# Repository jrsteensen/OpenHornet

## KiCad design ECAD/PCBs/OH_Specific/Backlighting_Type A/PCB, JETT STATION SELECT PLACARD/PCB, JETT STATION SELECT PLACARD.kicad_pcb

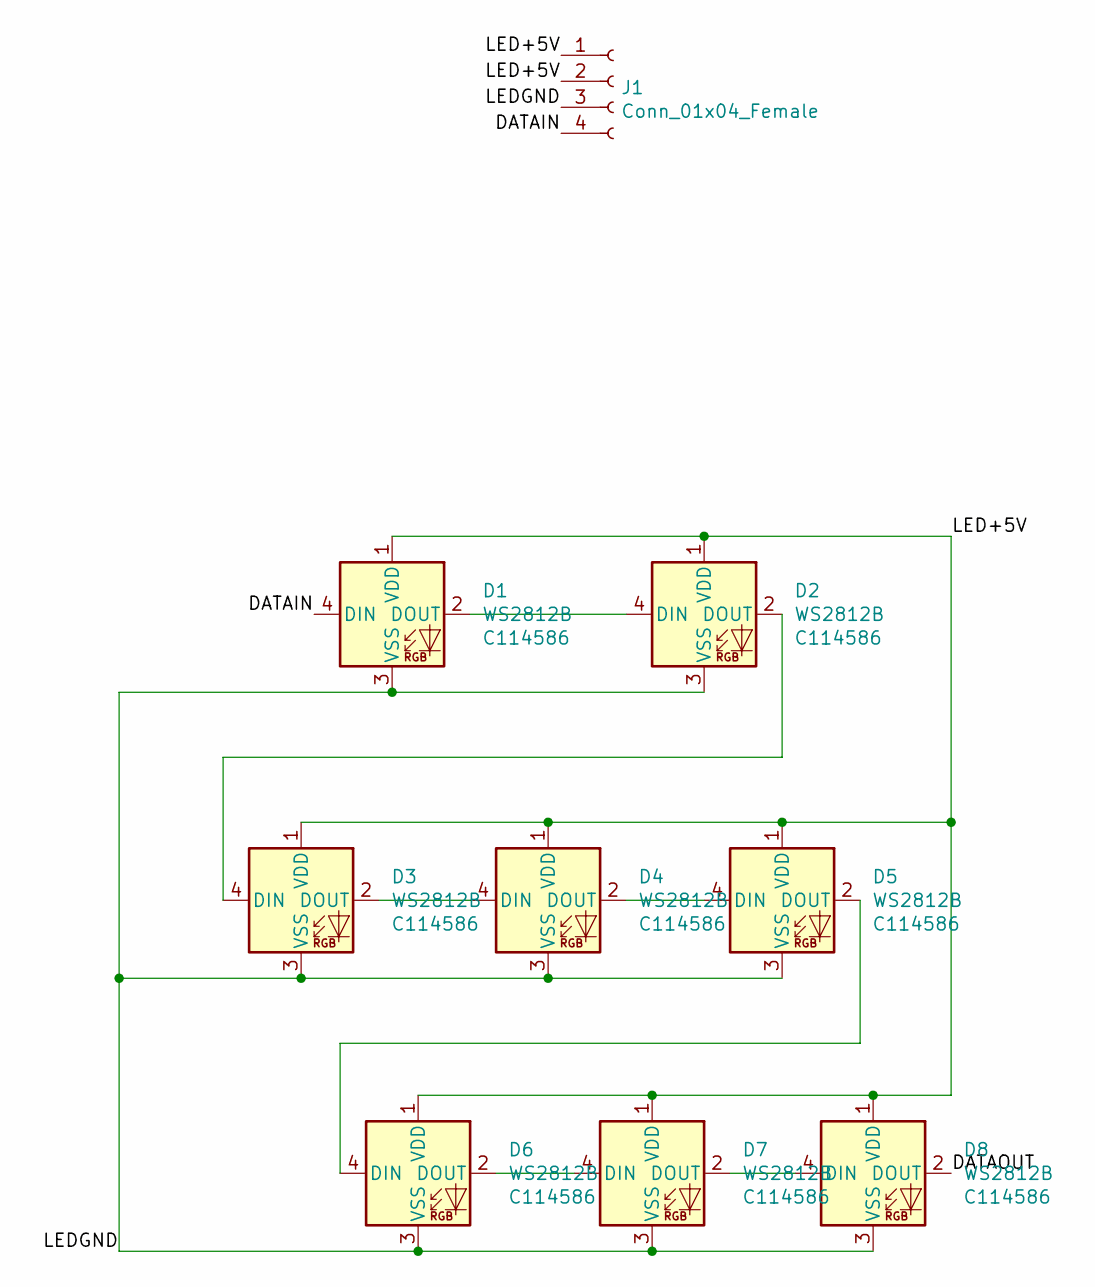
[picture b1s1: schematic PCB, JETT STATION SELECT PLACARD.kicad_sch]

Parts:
D1, D2, D3, D4, D5, D6, D7, D8: WS2812B; LED_WS2812B_PLCC4_5.0x5.0mm_P3.2mm; LCSC Part Number C114586
J1: Conn_01x04_Female; Molex_Mini-Fit_Jr_5566-04A_2x02_P4.20mm_Vertical

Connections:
/DATAIN: D1.4 (DIN), J1.4
/DATAOUT: D8.2 (DOUT)
/LED+5V: D1.1 (VDD), D2.1 (VDD), D3.1 (VDD), D4.1 (VDD), D5.1 (VDD), D6.1 (VDD), D7.1 (VDD), D8.1 (VDD), J1.1, J1.2
/LEDGND: D1.3 (VSS), D2.3 (VSS), D3.3 (VSS), D4.3 (VSS), D5.3 (VSS), D6.3 (VSS), D7.3 (VSS), D8.3 (VSS), J1.3
unnamed: D1.2 (DOUT), D2.4 (DIN)
unnamed: D2.2 (DOUT), D3.4 (DIN)
unnamed: D3.2 (DOUT), D4.4 (DIN)
unnamed: D4.2 (DOUT), D5.4 (DIN)
unnamed: D5.2 (DOUT), D6.4 (DIN)
unnamed: D6.2 (DOUT), D7.4 (DIN)
unnamed: D7.2 (DOUT), D8.4 (DIN)

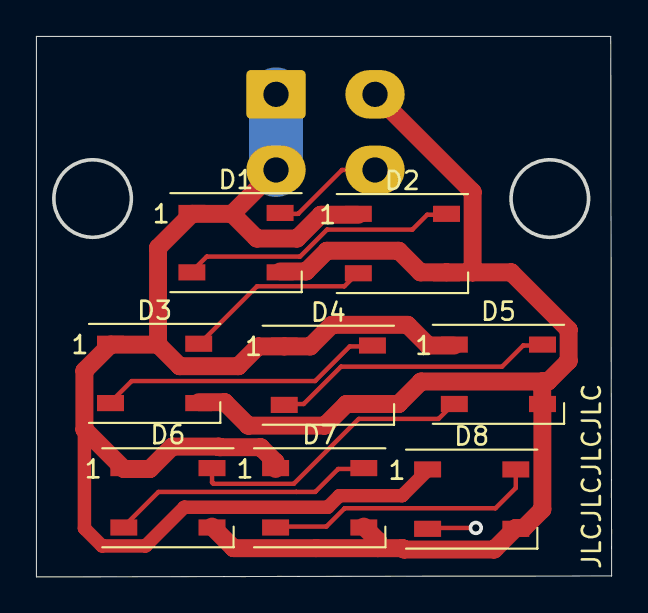
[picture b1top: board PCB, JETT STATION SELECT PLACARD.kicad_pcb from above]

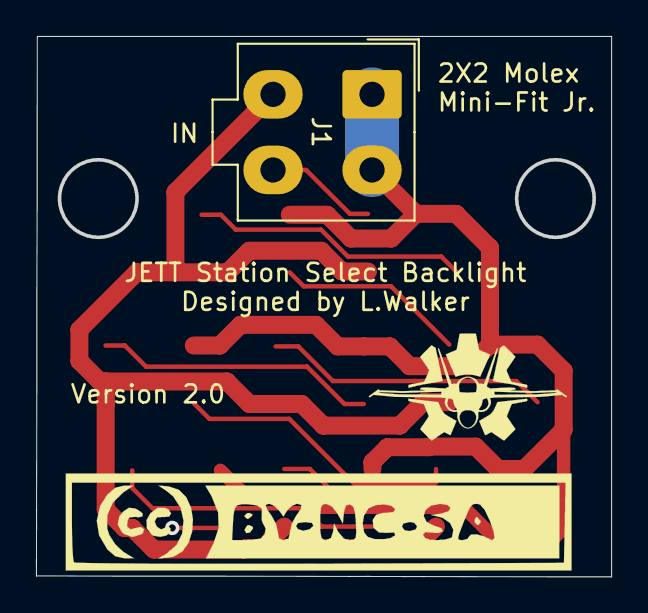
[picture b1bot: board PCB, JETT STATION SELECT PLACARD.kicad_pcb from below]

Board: 2 copper layers, 32.0 x 30.0 mm, 11 parts (3 on the bottom side), 10 nets.

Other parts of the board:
G1: OH_LOGO_ONLY_11x6mm
G2: LOGO; CC-BY-NC-SA-Small

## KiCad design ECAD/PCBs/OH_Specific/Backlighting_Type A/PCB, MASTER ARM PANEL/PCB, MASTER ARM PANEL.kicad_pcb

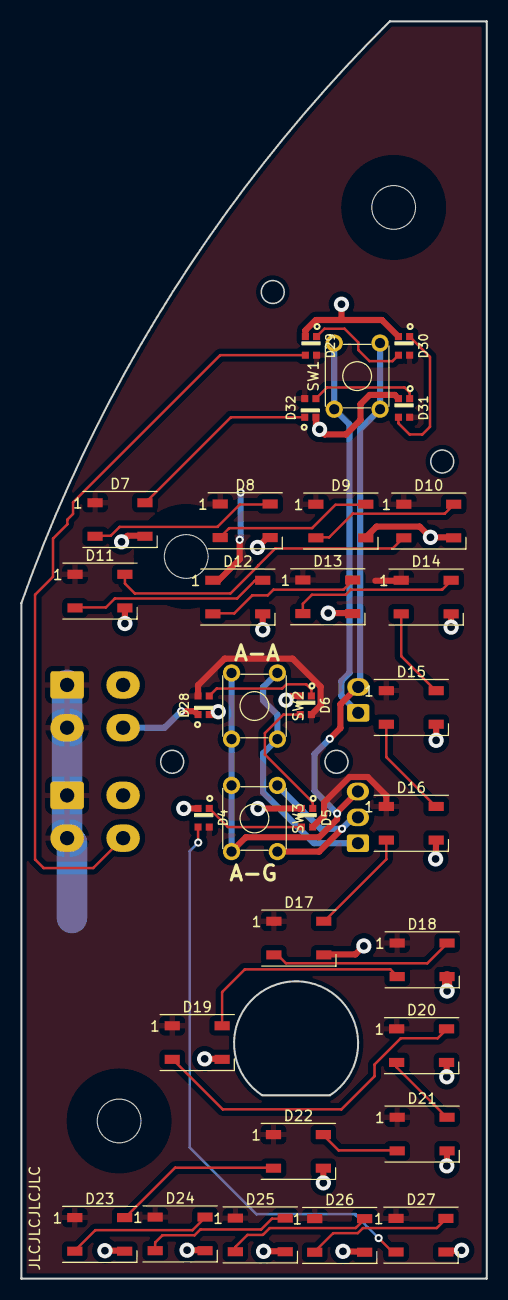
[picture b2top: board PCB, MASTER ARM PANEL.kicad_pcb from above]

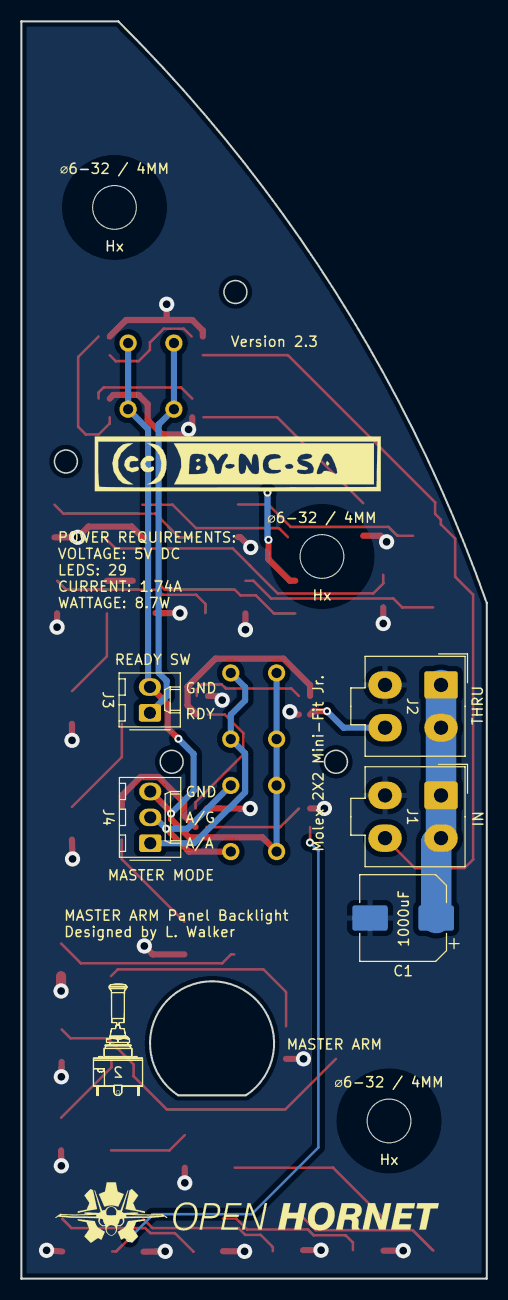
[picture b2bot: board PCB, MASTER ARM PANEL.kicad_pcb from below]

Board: 2 copper layers, 45.7 x 123.5 mm, 43 parts (7 on the bottom side), 36 nets.

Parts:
C1: C_Polarized; CP_Elec_8x10
D4, D5, D6, D28, D29, D30, D31, D32: WS2812B-2020; WS2812-2020
D7, D8, D9, D10, D11, D12, D13, D14, D15, D16, D17, D18, D19, D20, D21, D22, D23, D24, D25, D26, D27: WS2812B; LED_WS2812B_PLCC4_5.0x5.0mm_P3.2mm
H1, H2, H3: OHPanelScrew; OH_Panel_6-32_PHS
J1: BL IN; Molex_Mini-Fit_Jr_5566-04A_2x02_P4.20mm_Vertical
J2: BL OUT; Molex_Mini-Fit_Jr_5566-04A_2x02_P4.20mm_Vertical
J3: READY; Molex_KK-254_AE-6410-02A_1x02_P2.54mm_Vertical
J4: MASTER MODE; Molex_KK-254_AE-6410-03A_1x03_P2.54mm_Vertical
LOGO1: CC-BY-NC-SA_Icon; CC-BY-NC-SA-Small
LOGO2: OpenHornetLogoSmall; OH_LOGO_37.7mm_5.9mm
LOGO3: OH_S2AL_Silkscreen; S2AL_Toggle_Silkscreen
SW1: READY; SW_TH_Tactile_Omron_B3F-10xx
SW2: A/A; SW_TH_Tactile_Omron_B3F-10xx
SW3: A/G; SW_TH_Tactile_Omron_B3F-10xx

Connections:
/AA_SW: J4.1, SW2.1, SW2.2
/AG_SW: J4.2, SW3.1, SW3.2
/DATAIN: D29.3 (DIN), J1.4
/DATAOUT: D28.1 (DOUT), J2.4
/LED+5V: C1.1, D4.4 (VSS), D5.4 (VSS), D6.4 (VSS), D7.1 (VDD), D8.1 (VDD), D9.1 (VDD), D10.1 (VDD), D11.1 (VDD), D12.1 (VDD), D13.1 (VDD), D14.1 (VDD), D15.1 (VDD), D16.1 (VDD), D17.1 (VDD), D18.1 (VDD), D19.1 (VDD), D20.1 (VDD), D21.1 (VDD), D22.1 (VDD), D23.1 (VDD), D24.1 (VDD), D25.1 (VDD), D26.1 (VDD), D27.1 (VDD), D28.4 (VSS), D29.4 (VSS), D30.4 (VSS), D31.4 (VSS), D32.4 (VSS), J1.1, J1.2, J2.1, J2.2
/LEDGND: C1.2, D4.2 (GND), D5.2 (GND), D6.2 (GND), D7.3 (VSS), D8.3 (VSS), D9.3 (VSS), D10.3 (VSS), D11.3 (VSS), D12.3 (VSS), D13.3 (VSS), D14.3 (VSS), D15.3 (VSS), D16.3 (VSS), D17.3 (VSS), D18.3 (VSS), D19.3 (VSS), D20.3 (VSS), D21.3 (VSS), D22.3 (VSS), D23.3 (VSS), D24.3 (VSS), D25.3 (VSS), D26.3 (VSS), D27.3 (VSS), D28.2 (GND), D29.2 (GND), D30.2 (GND), D31.2 (GND), D32.2 (GND), J1.3, J2.3
/READY_SW: J3.1, SW1.1, SW1.2
GND: J3.2, J4.3, SW1.3, SW1.4, SW2.3, SW2.4, SW3.3, SW3.4
unnamed: D4.1 (DOUT), D5.3 (DIN)
unnamed: D5.1 (DOUT), D6.3 (DIN)
unnamed: D7.2 (DOUT), D8.4 (DIN)
unnamed: D8.2 (DOUT), D9.4 (DIN)
unnamed: D10.2 (DOUT), D11.4 (DIN)
unnamed: D9.2 (DOUT), D10.4 (DIN)
unnamed: D11.2 (DOUT), D12.4 (DIN)
unnamed: D12.2 (DOUT), D13.4 (DIN)
unnamed: D13.2 (DOUT), D14.4 (DIN)
unnamed: D14.2 (DOUT), D15.4 (DIN)
unnamed: D15.2 (DOUT), D16.4 (DIN)
unnamed: D16.2 (DOUT), D17.4 (DIN)
unnamed: D17.2 (DOUT), D18.4 (DIN)
unnamed: D18.2 (DOUT), D19.4 (DIN)
unnamed: D19.2 (DOUT), D20.4 (DIN)
unnamed: D20.2 (DOUT), D21.4 (DIN)
unnamed: D21.2 (DOUT), D22.4 (DIN)
unnamed: D22.2 (DOUT), D23.4 (DIN)
unnamed: D23.2 (DOUT), D24.4 (DIN)
unnamed: D24.2 (DOUT), D25.4 (DIN)
unnamed: D25.2 (DOUT), D26.4 (DIN)
unnamed: D26.2 (DOUT), D27.4 (DIN)
unnamed: D4.3 (DIN), D27.2 (DOUT)
unnamed: D6.1 (DOUT), D28.3 (DIN)
unnamed: D29.1 (DOUT), D30.3 (DIN)
unnamed: D30.1 (DOUT), D31.3 (DIN)
unnamed: D31.1 (DOUT), D32.3 (DIN)
unnamed: D7.4 (DIN), D32.1 (DOUT)

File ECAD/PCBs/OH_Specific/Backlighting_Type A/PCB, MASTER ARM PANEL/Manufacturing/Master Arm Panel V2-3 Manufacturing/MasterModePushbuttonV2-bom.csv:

Comment,Designator,Footprint,LCSC
C_Polarized,C1,Capacitor_SMD:CP_Elec_8x10,
WS2812B-2020,"D4,D5,D6,D28,D29,D30,D31,D32",KiCAD Libraries:WS2812-2020,C965555
WS2812B,"D7,D8,D9,D10,D11,D12,D13,D14,D15,D16,D17,D18,D19,D20,D21,D22,D23,D24,D25,D26,D27",LED_SMD:LED_WS2812B_PLCC4_5.0x5.0mm_P3.2mm,C2761795
BL IN,J1,Connector_Molex:Molex_Mini-Fit_Jr_5566-04A_2x02_P4.20mm_Vertical,
BL OUT,J2,Connector_Molex:Molex_Mini-Fit_Jr_5566-04A_2x02_P4.20mm_Vertical,
READY,J3,Connector_Molex:Molex_KK-254_AE-6410-02A_1x02_P2.54mm_Vertical,
MASTER MODE,J4,Connector_Molex:Molex_KK-254_AE-6410-03A_1x03_P2.54mm_Vertical,
READY,SW1,Button_Switch_THT:SW_TH_Tactile_Omron_B3F-10xx,
A/A,SW2,Button_Switch_THT:SW_TH_Tactile_Omron_B3F-10xx,
A/G,SW3,Button_Switch_THT:SW_TH_Tactile_Omron_B3F-10xx,

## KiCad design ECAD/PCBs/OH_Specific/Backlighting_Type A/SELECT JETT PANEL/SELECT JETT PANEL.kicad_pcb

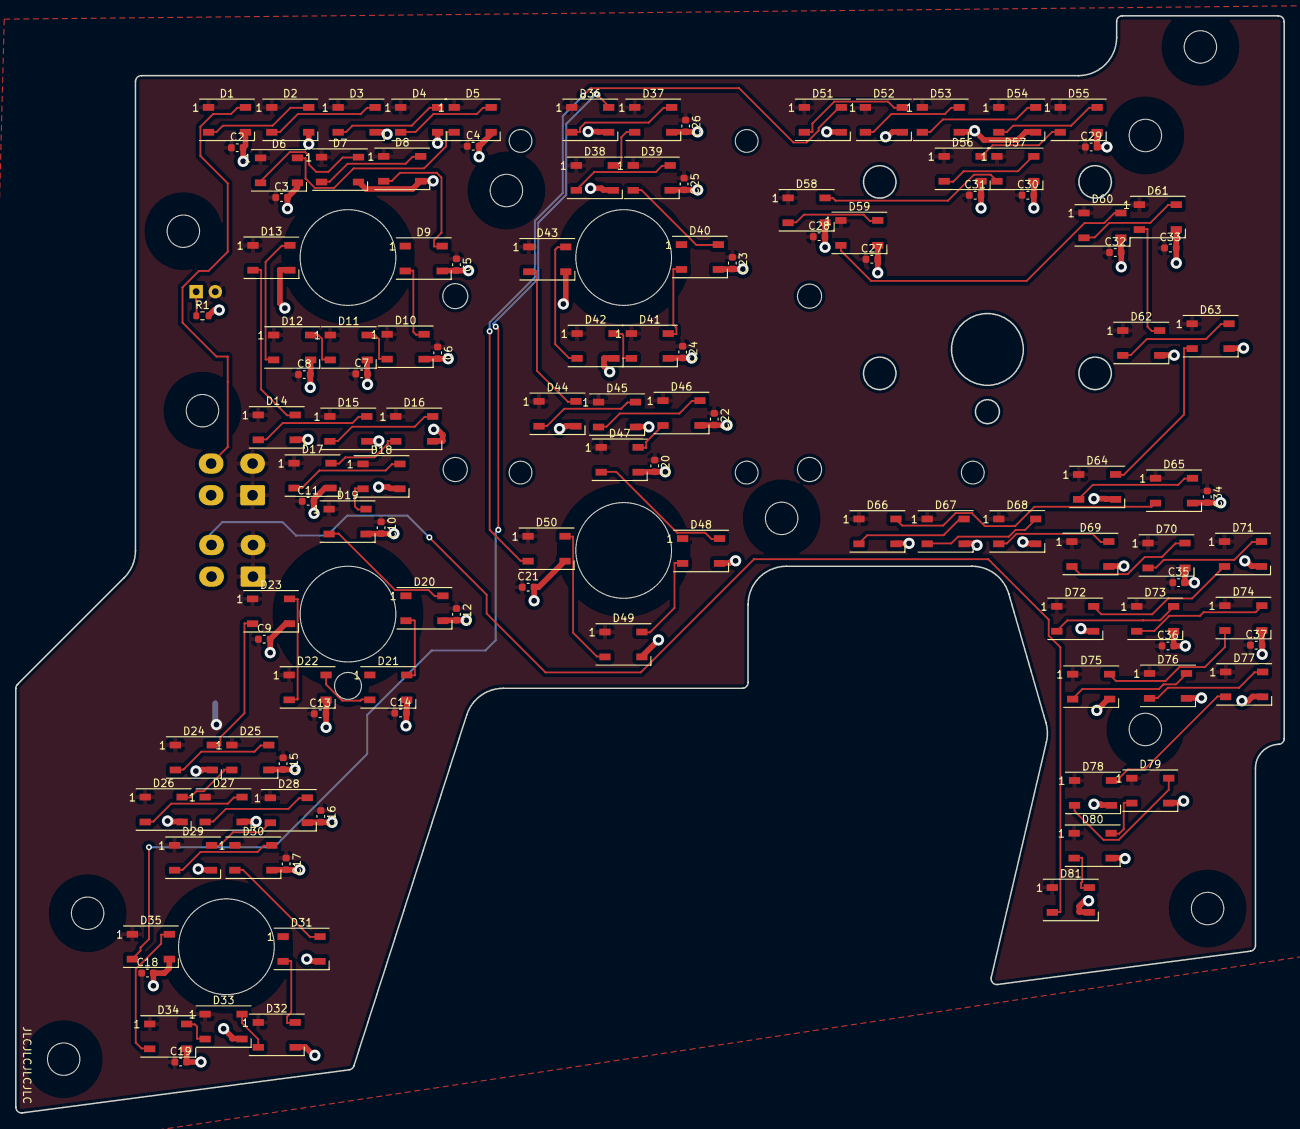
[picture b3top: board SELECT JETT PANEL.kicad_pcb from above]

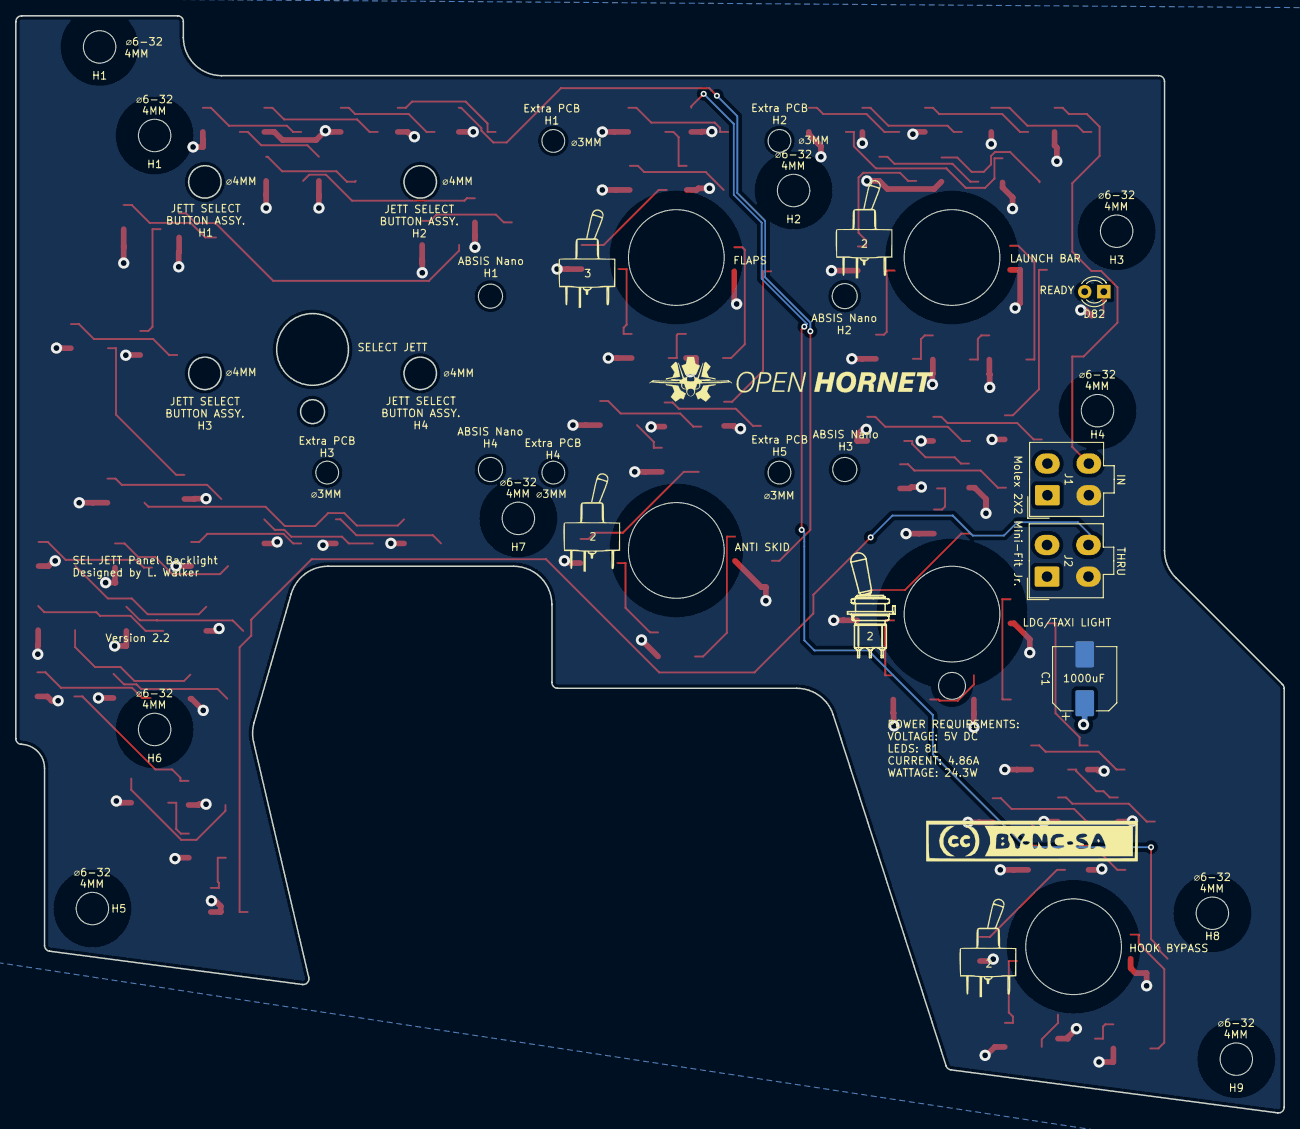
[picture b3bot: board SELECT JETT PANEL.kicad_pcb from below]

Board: 2 copper layers, 168.3 x 145.6 mm, 142 parts (6 on the bottom side), 85 nets.

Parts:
1, 2, 3, 3#2, 4, 5, 6, 7, 8, 9: OH_Panel_Fastner_Keepout; OH_Panel_6-32_PHS
10: LOGO; CC-BY-NC-SA-Small
11: LOGO; OH_LOGO_37.7mm_5.9mm
12, 13: 631H Toggle; 631H_Toggle_Silkscreen
14: 100SP1 Toggle; 100SP1_Toggle_Silkscreen
15, 16, 17, 18: 631H_Toggle_13mm_x_13mm
16#2: 100SPX_Toggle_13mm_x_18mm
C1: C_Polarized; CP_Elec_8x10
C2, C3, C4, C5, C6, C7, C8, C9, C10, C11, C12, C13, C14, C15, C16, C17, C18, C19, C20, C21, C22, C23, C24, C25, C26, C27, C28, C29, C30, C31, C32, C33, C34, C35, C36, C37: C; C_0603_1608Metric
D1, D2, D3, D4, D5, D6, D7, D8, D9, D10, D11, D12, D13, D14, D15, D16, D17, D18, D19, D20, D21, D22, D23, D24, D25, D26, D27, D28, D29, D30, D31, D32, D33, D34, D35, D36, D37, D38, D39, D40, D41, D42, D43, D44, D45, D46, D47, D48, D49, D50, D51, D52, D53, D54, D55, D56, D57, D58, D59, D60, D61, D62, D63, D64, D65, D66, D67, D68, D69, D70, D71, D72, D73, D74, D75, D76, D77, D78, D79, D80, D81: WS2812B; LED_WS2812B_PLCC4_5.0x5.0mm_P3.2mm
D82: LED; LED_D3.0mm
J1, J2: Conn_01x04_Female; Molex_Mini-Fit_Jr_5566-04A_2x02_P4.20mm_Vertical
R1: R; R_0603_1608Metric

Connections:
/DATAIN: D1.4 (DIN), J1.4
/DATAOUT: D81.2 (DOUT), J2.4
/LED+5V: C1.1, C2.1, C3.1, C4.1, C5.1, C6.1, C7.1, C8.1, C9.1, C10.1, C11.1, C12.1, C13.1, C14.1, C15.1, C16.1, C17.1, C18.1, C19.1, C20.1, C21.1, C22.1, C23.1, C24.1, C25.1, C26.1, C27.1, C28.1, C29.1, C30.1, C31.1, C32.1, C33.1, C34.1, C35.1, C36.1, C37.1, D1.1 (VDD), D2.1 (VDD), D3.1 (VDD), D4.1 (VDD), D5.1 (VDD), D6.1 (VDD), D7.1 (VDD), D8.1 (VDD), D9.1 (VDD), D10.1 (VDD), D11.1 (VDD), D12.1 (VDD), D13.1 (VDD), D14.1 (VDD), D15.1 (VDD), D16.1 (VDD), D17.1 (VDD), D18.1 (VDD), D19.1 (VDD), D20.1 (VDD), D21.1 (VDD), D22.1 (VDD), D23.1 (VDD), D24.1 (VDD), D25.1 (VDD), D26.1 (VDD), D27.1 (VDD), D28.1 (VDD), D29.1 (VDD), D30.1 (VDD), D31.1 (VDD), D32.1 (VDD), D33.1 (VDD), D34.1 (VDD), D35.1 (VDD), D36.1 (VDD), D37.1 (VDD), D38.1 (VDD), D39.1 (VDD), D40.1 (VDD), D41.1 (VDD), D42.1 (VDD), D43.1 (VDD), D44.1 (VDD), D45.1 (VDD), D46.1 (VDD), D47.1 (VDD), D48.1 (VDD), D49.1 (VDD), D50.1 (VDD), D51.1 (VDD), D52.1 (VDD), D53.1 (VDD), D54.1 (VDD), D55.1 (VDD), D56.1 (VDD), D57.1 (VDD), D58.1 (VDD), D59.1 (VDD), D60.1 (VDD), D61.1 (VDD), D62.1 (VDD), D63.1 (VDD), D64.1 (VDD), D65.1 (VDD), D66.1 (VDD), D67.1 (VDD), D68.1 (VDD), D69.1 (VDD), D70.1 (VDD), D71.1 (VDD), D72.1 (VDD), D73.1 (VDD), D74.1 (VDD), D75.1 (VDD), D76.1 (VDD), D77.1 (VDD), D78.1 (VDD), D79.1 (VDD), D80.1 (VDD), D81.1 (VDD), D82.2 (A), J1.1, J1.2, J2.1, J2.2
/LEDGND: C1.2, C2.2, C3.2, C4.2, C5.2, C6.2, C7.2, C8.2, C9.2, C10.2, C11.2, C12.2, C13.2, C14.2, C15.2, C16.2, C17.2, C18.2, C19.2, C20.2, C21.2, C22.2, C23.2, C24.2, C25.2, C26.2, C27.2, C28.2, C29.2, C30.2, C31.2, C32.2, C33.2, C34.2, C35.2, C36.2, C37.2, D1.3 (VSS), D2.3 (VSS), D3.3 (VSS), D4.3 (VSS), D5.3 (VSS), D6.3 (VSS), D7.3 (VSS), D8.3 (VSS), D9.3 (VSS), D10.3 (VSS), D11.3 (VSS), D12.3 (VSS), D13.3 (VSS), D14.3 (VSS), D15.3 (VSS), D16.3 (VSS), D17.3 (VSS), D18.3 (VSS), D19.3 (VSS), D20.3 (VSS), D21.3 (VSS), D22.3 (VSS), D23.3 (VSS), D24.3 (VSS), D25.3 (VSS), D26.3 (VSS), D27.3 (VSS), D28.3 (VSS), D29.3 (VSS), D30.3 (VSS), D31.3 (VSS), D32.3 (VSS), D33.3 (VSS), D34.3 (VSS), D35.3 (VSS), D36.3 (VSS), D37.3 (VSS), D38.3 (VSS), D39.3 (VSS), D40.3 (VSS), D41.3 (VSS), D42.3 (VSS), D43.3 (VSS), D44.3 (VSS), D45.3 (VSS), D46.3 (VSS), D47.3 (VSS), D48.3 (VSS), D49.3 (VSS), D50.3 (VSS), D51.3 (VSS), D52.3 (VSS), D53.3 (VSS), D54.3 (VSS), D55.3 (VSS), D56.3 (VSS), D57.3 (VSS), D58.3 (VSS), D59.3 (VSS), D60.3 (VSS), D61.3 (VSS), D62.3 (VSS), D63.3 (VSS), D64.3 (VSS), D65.3 (VSS), D66.3 (VSS), D67.3 (VSS), D68.3 (VSS), D69.3 (VSS), D70.3 (VSS), D71.3 (VSS), D72.3 (VSS), D73.3 (VSS), D74.3 (VSS), D75.3 (VSS), D76.3 (VSS), D77.3 (VSS), D78.3 (VSS), D79.3 (VSS), D80.3 (VSS), D81.3 (VSS), J1.3, J2.3, R1.2
unnamed: D1.2 (DOUT), D2.4 (DIN)
unnamed: D2.2 (DOUT), D3.4 (DIN)
unnamed: D3.2 (DOUT), D4.4 (DIN)
unnamed: D4.2 (DOUT), D5.4 (DIN)
unnamed: D5.2 (DOUT), D6.4 (DIN)
unnamed: D6.2 (DOUT), D7.4 (DIN)
unnamed: D7.2 (DOUT), D8.4 (DIN)
unnamed: D8.2 (DOUT), D9.4 (DIN)
unnamed: D10.2 (DOUT), D11.4 (DIN)
unnamed: D9.2 (DOUT), D10.4 (DIN)
unnamed: D11.2 (DOUT), D12.4 (DIN)
unnamed: D12.2 (DOUT), D13.4 (DIN)
unnamed: D13.2 (DOUT), D14.4 (DIN)
unnamed: D14.2 (DOUT), D15.4 (DIN)
unnamed: D15.2 (DOUT), D16.4 (DIN)
unnamed: D16.2 (DOUT), D17.4 (DIN)
unnamed: D17.2 (DOUT), D18.4 (DIN)
unnamed: D18.2 (DOUT), D19.4 (DIN)
unnamed: D19.2 (DOUT), D20.4 (DIN)
unnamed: D20.2 (DOUT), D21.4 (DIN)
unnamed: D21.2 (DOUT), D22.4 (DIN)
unnamed: D22.2 (DOUT), D23.4 (DIN)
unnamed: D23.2 (DOUT), D24.4 (DIN)
unnamed: D24.2 (DOUT), D25.4 (DIN)
unnamed: D25.2 (DOUT), D26.4 (DIN)
unnamed: D26.2 (DOUT), D27.4 (DIN)
unnamed: D27.2 (DOUT), D28.4 (DIN)
unnamed: D28.2 (DOUT), D29.4 (DIN)
unnamed: D29.2 (DOUT), D30.4 (DIN)
unnamed: D30.2 (DOUT), D31.4 (DIN)
unnamed: D31.2 (DOUT), D32.4 (DIN)
unnamed: D32.2 (DOUT), D33.4 (DIN)
unnamed: D33.2 (DOUT), D34.4 (DIN)
unnamed: D34.2 (DOUT), D35.4 (DIN)
unnamed: D35.2 (DOUT), D36.4 (DIN)
unnamed: D36.2 (DOUT), D37.4 (DIN)
unnamed: D37.2 (DOUT), D38.4 (DIN)
unnamed: D38.2 (DOUT), D39.4 (DIN)
unnamed: D39.2 (DOUT), D40.4 (DIN)
unnamed: D40.2 (DOUT), D41.4 (DIN)
unnamed: D41.2 (DOUT), D42.4 (DIN)
unnamed: D42.2 (DOUT), D43.4 (DIN)
unnamed: D43.2 (DOUT), D44.4 (DIN)
unnamed: D44.2 (DOUT), D45.4 (DIN)
unnamed: D45.2 (DOUT), D46.4 (DIN)
unnamed: D46.2 (DOUT), D47.4 (DIN)
unnamed: D47.2 (DOUT), D48.4 (DIN)
unnamed: D48.2 (DOUT), D49.4 (DIN)
unnamed: D49.2 (DOUT), D50.4 (DIN)
unnamed: D50.2 (DOUT), D51.4 (DIN)
unnamed: D51.2 (DOUT), D52.4 (DIN)
unnamed: D52.2 (DOUT), D53.4 (DIN)
unnamed: D53.2 (DOUT), D54.4 (DIN)
unnamed: D54.2 (DOUT), D55.4 (DIN)
unnamed: D55.2 (DOUT), D56.4 (DIN)
unnamed: D56.2 (DOUT), D57.4 (DIN)
unnamed: D57.2 (DOUT), D58.4 (DIN)
unnamed: D58.2 (DOUT), D59.4 (DIN)
unnamed: D59.2 (DOUT), D60.4 (DIN)
unnamed: D60.2 (DOUT), D61.4 (DIN)
unnamed: D61.2 (DOUT), D62.4 (DIN)
unnamed: D62.2 (DOUT), D63.4 (DIN)
unnamed: D63.2 (DOUT), D64.4 (DIN)
unnamed: D64.2 (DOUT), D65.4 (DIN)
unnamed: D65.2 (DOUT), D66.4 (DIN)
unnamed: D66.2 (DOUT), D67.4 (DIN)
unnamed: D67.2 (DOUT), D68.4 (DIN)
unnamed: D68.2 (DOUT), D69.4 (DIN)
unnamed: D69.2 (DOUT), D70.4 (DIN)
unnamed: D70.2 (DOUT), D71.4 (DIN)
unnamed: D71.2 (DOUT), D72.4 (DIN)
unnamed: D72.2 (DOUT), D73.4 (DIN)
unnamed: D73.2 (DOUT), D74.4 (DIN)
unnamed: D74.2 (DOUT), D75.4 (DIN)
unnamed: D75.2 (DOUT), D76.4 (DIN)
unnamed: D76.2 (DOUT), D77.4 (DIN)
unnamed: D77.2 (DOUT), D78.4 (DIN)
unnamed: D78.2 (DOUT), D79.4 (DIN)
unnamed: D79.2 (DOUT), D80.4 (DIN)
unnamed: D80.2 (DOUT), D81.4 (DIN)
unnamed: D82.1 (K), R1.1

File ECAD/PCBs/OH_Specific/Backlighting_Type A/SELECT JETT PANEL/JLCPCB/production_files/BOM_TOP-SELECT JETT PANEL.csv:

Comment,Designator,Footprint,LCSC
C,"C10,C11,C12,C13,C14,C15,C16,C17,C18,C19,C2,C20,C21,C22,C23,C24,C25,C26,C27,C28,C29,C3,C30,C31,C32,C33,C34,C35,C36,C37,C4,C5,C6,C7,C8,C9",C_0603_1608Metric,C14663
R,R1,R_0603_1608Metric,C23179
WS2812B,"D1,D10,D11,D12,D13,D14,D15,D16,D17,D18,D19,D2,D20,D21,D22,D23,D24,D25,D26,D27,D28,D29,D3,D30,D31,D32,D33,D34,D35,D36,D37,D38,D39,D4,D40,D41,D42,D43,D44,D45,D46,D47,D48,D49,D5,D50,D51,D52,D53,D54,D55,D56,D57,D58,D59,D6,D60,D61,D62,D63,D64,D65,D66,D67,D68,D69,D7,D70,D71,D72,D73,D74,D75,D76,D77,D78,D79,D8,D80,D81,D9",LED_WS2812B_PLCC4_5.0x5.0mm_P3.2mm,C2761795
